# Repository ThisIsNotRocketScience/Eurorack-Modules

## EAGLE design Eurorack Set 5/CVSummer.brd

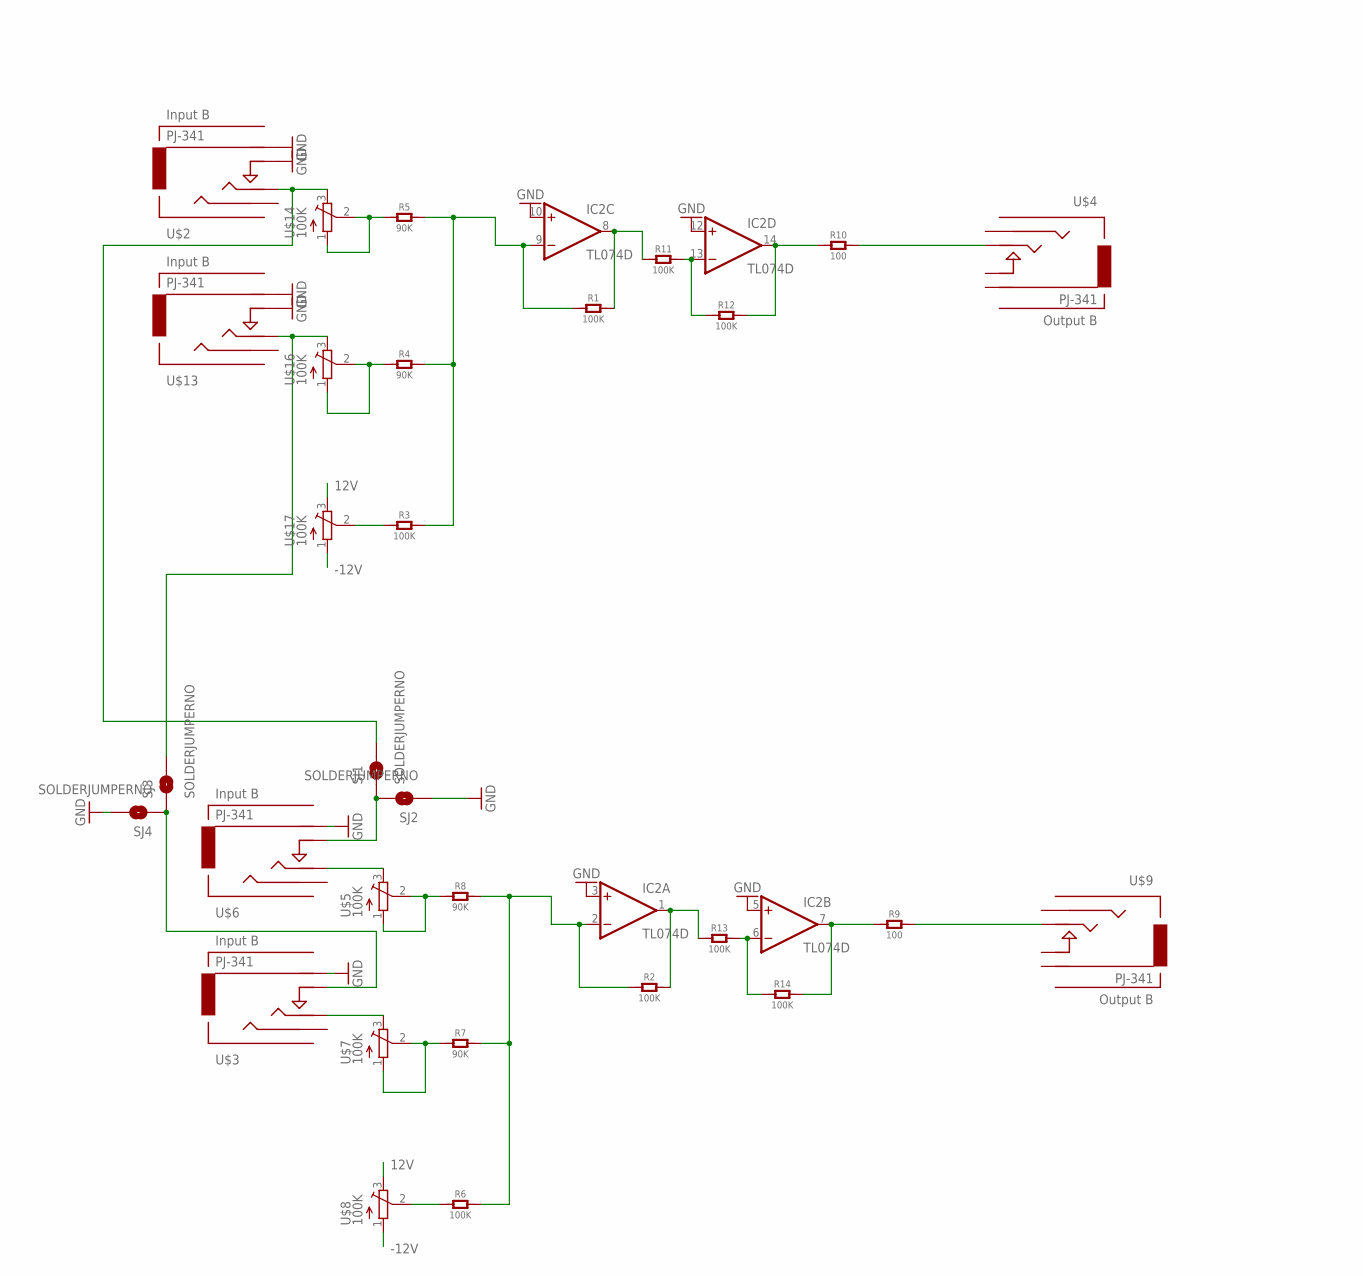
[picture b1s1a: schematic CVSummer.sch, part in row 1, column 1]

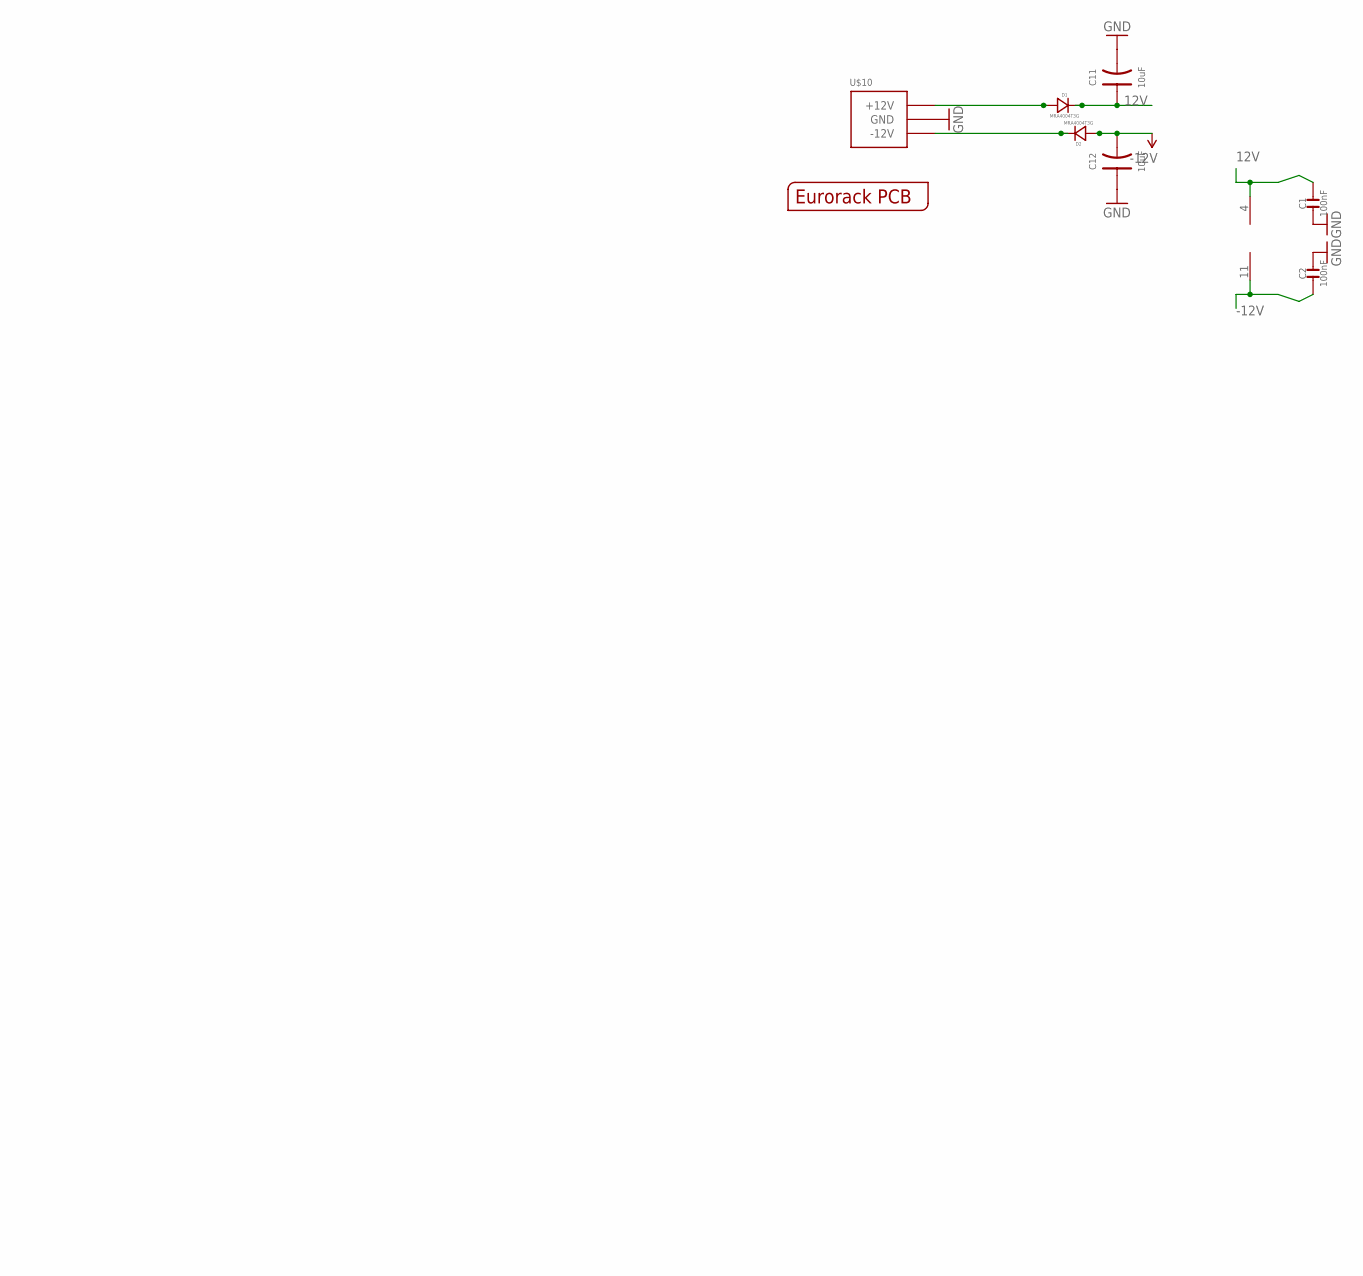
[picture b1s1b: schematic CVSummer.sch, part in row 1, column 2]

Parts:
C1, C2: 100nF; C0603
C11, C12: 10uF; AVX-A
D1, D2: MRA4004T3G; DO-214AC; MPN US1G-E3/5AT
IC2: TL074D; SO14
R1, R2, R3, R6, R11, R12, R13, R14: 100K; C0805
R4, R5, R7, R8: 90K; C0805
R9, R10: 100; C0805
SJ1, SJ2, SJ3, SJ4: SOLDERJUMPERNO; SJ_2S-NO
U$1: EURORACK_PCB4HP; EURORACK4HPPCB
U$2, U$3, U$6, U$13: PJ-341; 3.5MM-JACK-SWITCH-13MM-INPUT
U$4, U$9: PJ-341; 3.5MM-JACK-SWITCH-13MM-OUTPUT
U$5, U$7, U$8, U$14, U$16, U$17: 100K; TC33X
U$10: POWER_SIMPLE10; POWER_10

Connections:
12V: C1.2, C11.+ (1), D1.2 (-), IC2.4 (V+), U$8.3 (E), U$17.3 (E)
-12V: C2.1, C12.- (2), D2.1 (+), IC2.11 (V-), U$8.1 (A), U$17.1 (A)
GND: C1.1, C2.2, C11.- (2), C12.+ (1), IC2.3 (+IN), IC2.5 (+IN), IC2.10 (+IN), IC2.12 (+IN), SJ2.1, SJ4.2, U$2.RING@3 (RING), U$2.SWITCH@3 (SWITCH), U$3.RING@3 (RING), U$6.RING@3 (RING), U$10.3 (GND), U$10.4 (GND), U$10.5 (GND), U$10.6 (GND), U$10.7 (GND), U$10.8 (GND), U$13.RING@3 (RING), U$13.SWITCH@3 (SWITCH)
unnamed: SJ1.1, SJ2.2, U$6.SWITCH@3 (SWITCH)
unnamed: IC2.14 (OUT), R10.1, R12.2
unnamed: R5.1, U$14.1 (A), U$14.2 (S)
unnamed: U$5.3 (E), U$6.TIP@3 (TIP)
unnamed: IC2.7 (OUT), R9.1, R14.2
unnamed: R3.1, U$17.2 (S)
unnamed: IC2.8 (OUT), R1.2, R11.1
unnamed: IC2.13 (-IN), R11.2, R12.1
unnamed: R6.1, U$8.2 (S)
unnamed: R4.1, U$16.1 (A), U$16.2 (S)
unnamed: U$3.TIP@3 (TIP), U$7.3 (E)
unnamed: SJ3.2, U$13.TIP@3 (TIP), U$16.3 (E)
unnamed: IC2.2 (-IN), R2.1, R6.2, R7.2, R8.2
unnamed: IC2.9 (-IN), R1.1, R3.2, R4.2, R5.2
unnamed: R9.2, U$9.TIP@3 (TIP)
unnamed: R8.1, U$5.1 (A), U$5.2 (S)
unnamed: R7.1, U$7.1 (A), U$7.2 (S)
unnamed: IC2.1 (OUT), R2.2, R13.1
unnamed: IC2.6 (-IN), R13.2, R14.1
unnamed: SJ1.2, U$2.TIP@3 (TIP), U$14.3 (E)
unnamed: SJ3.1, SJ4.1, U$3.SWITCH@3 (SWITCH)
unnamed: R10.2, U$4.TIP@3 (TIP)
unnamed: D1.1 (+), U$10.9 (+12V), U$10.10 (+12V)
unnamed: D2.2 (-), U$10.1 (-12V), U$10.2 (-12V)

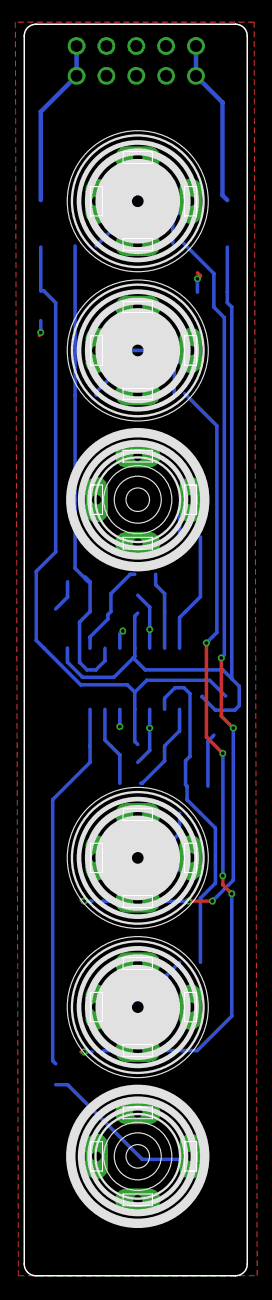
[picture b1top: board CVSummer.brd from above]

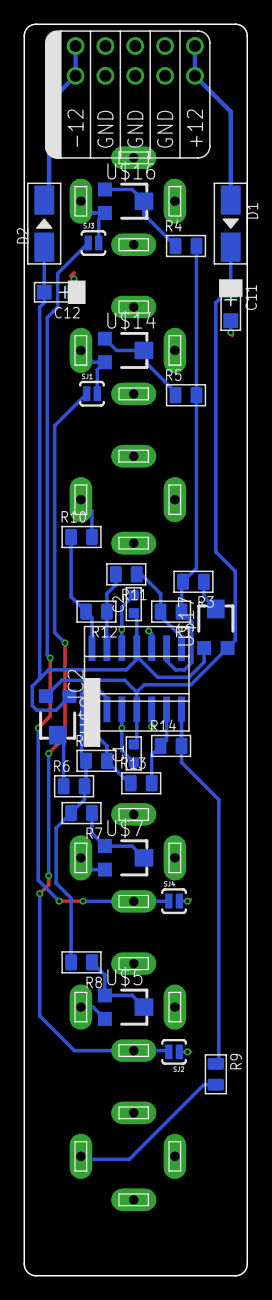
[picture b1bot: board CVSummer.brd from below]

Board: 2 copper layers, 19.0 x 106.5 mm, 39 parts (32 on the bottom side), 27 nets.

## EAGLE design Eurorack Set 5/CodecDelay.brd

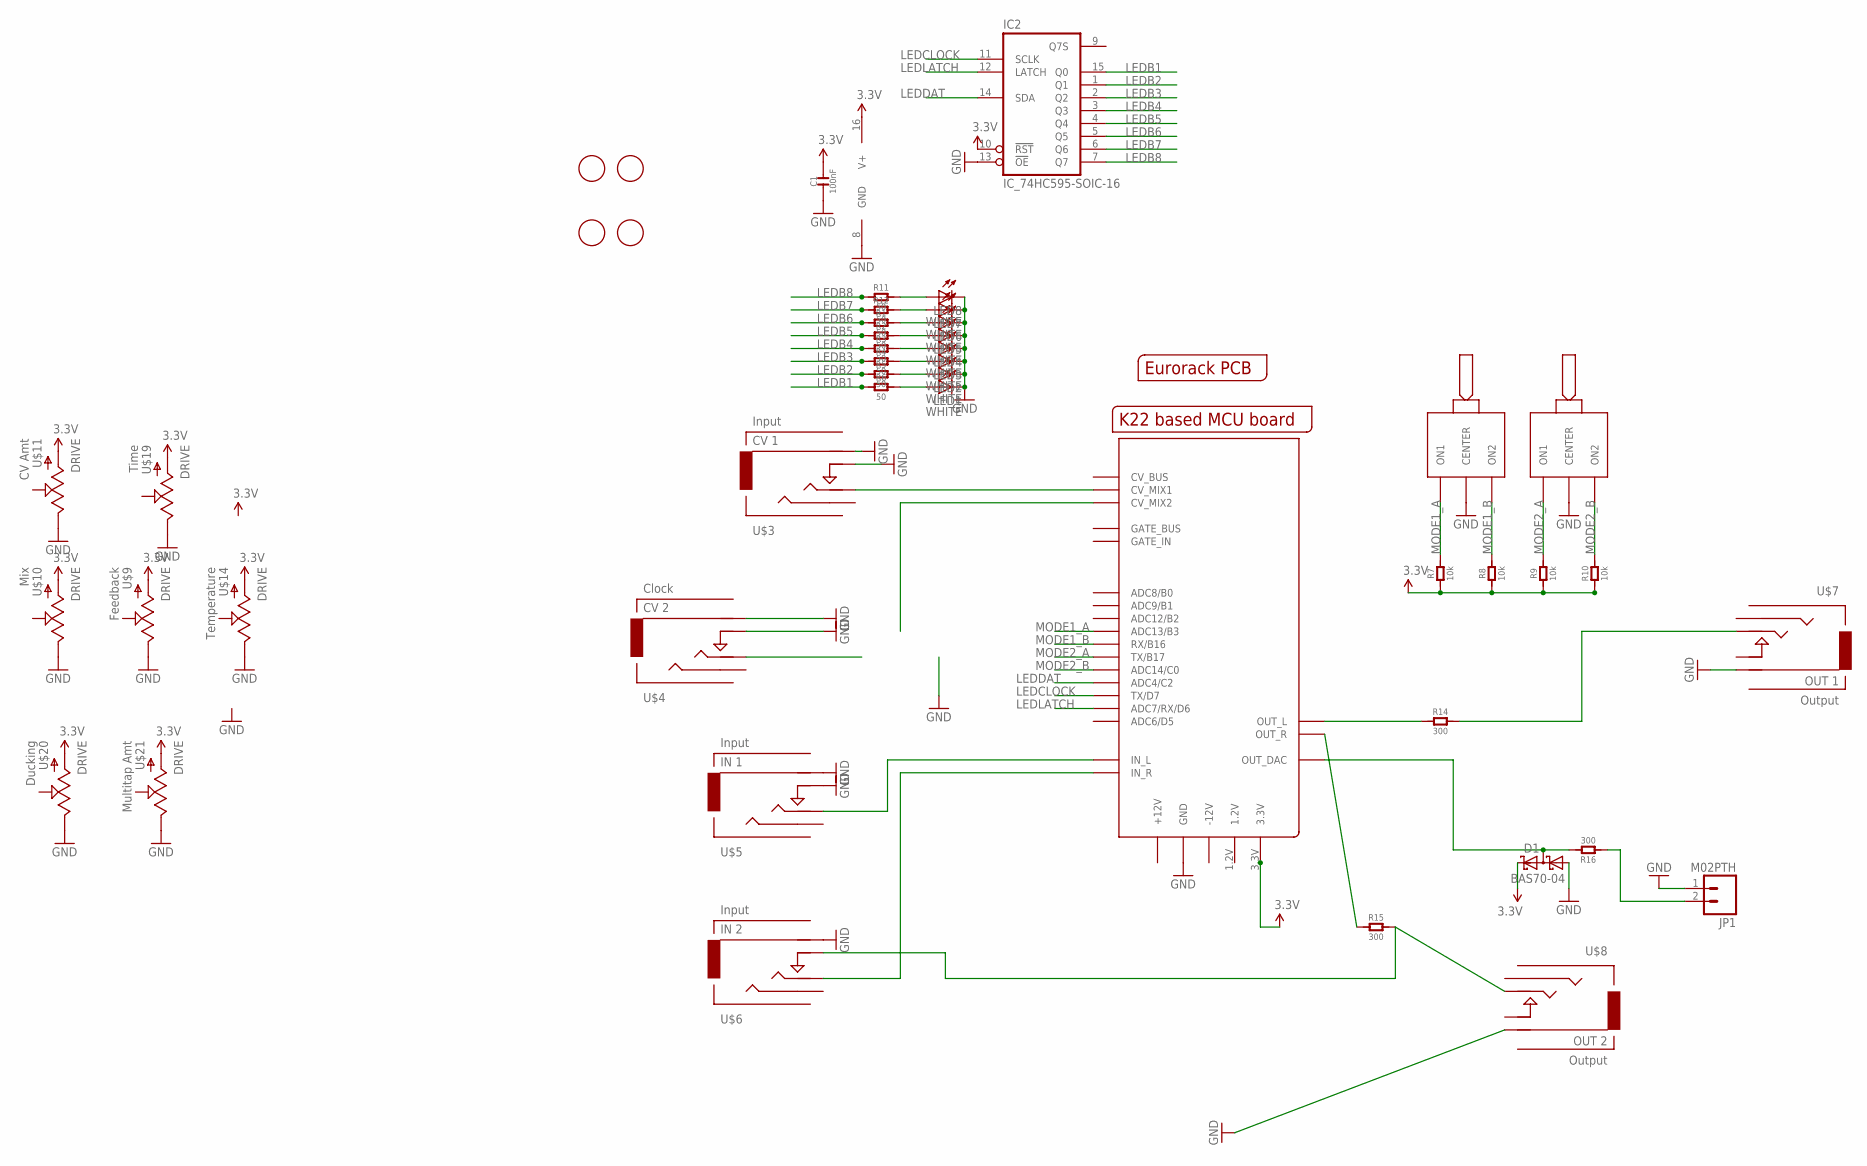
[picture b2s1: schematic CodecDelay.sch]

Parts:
C1: 100nF; C0603
D1: BAS70-04; SOT23
IC2: IC_74HC595-SOIC-16; SOIC-16
JP1: M02PTH; 1X02
LED1, LED2, LED3, LED4, LED5, LED6, LED7, LED8: WHITE; LED3MM
R1, R2, R3, R4, R5, R6, R11, R12: 50; R0603
R7, R8, R9, R10: 10k; R0603
R14, R15: 300; C0805
R16: 300; R0603
U$1: MCUBOARD; MCUBASEBOARD
U$2: EURORACK_PCB8HP; EURORACK8HPPCB
U$3: CV 1; 3.5MM-JACK-SWITCH-13MM-INPUT
U$4: CV 2; 3.5MM-JACK-SWITCH-13MM-INPUT
U$5: IN 1; 3.5MM-JACK-SWITCH-13MM-INPUT
U$6: IN 2; 3.5MM-JACK-SWITCH-13MM-INPUT
U$7: OUT 1; 3.5MM-JACK-SWITCH-13MM-OUTPUT
U$8: OUT 2; 3.5MM-JACK-SWITCH-13MM-OUTPUT
U$9, U$10, U$11, U$14, U$19, U$20, U$21: DRIVE; OG-POTS_ALPS_POT_VERTICAL
U$12, U$13: ONOFFON; MULTICOMP1MS-ONOFFON
U$15, U$16, U$17, U$18: FIDUCIAL; FIDUCIAL_1MM

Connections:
3.3V: C1.2, D1.2 (C2), IC2.10 (!RST), IC2.16 (V+), R7.1, R8.1, R9.1, R10.1, U$1.3.3V, U$9.P$3 (A), U$10.P$3 (A), U$11.P$3 (A), U$14.P$3 (A), U$19.P$3 (A), U$20.P$3 (A), U$21.P$3 (A)
GND: C1.1, D1.1 (A1), IC2.8 (GND), IC2.13 (!OE), JP1.1, LED1.K (C), LED2.K (C), LED3.K (C), LED4.K (C), LED5.K (C), LED6.K (C), LED7.K (C), LED8.K (C), U$1.GND@1 (GND), U$1.GND@2 (GND), U$1.GND@4 (GND), U$1.GND@5 (GND), U$1.GND@6 (GND), U$1.GND@7 (GND), U$1.GND@8 (GND), U$1.GND@9 (GND), U$1.GND_BUS (GND), U$3.RING@3 (RING), U$3.SWITCH@3 (SWITCH), U$4.RING@3 (RING), U$4.SWITCH@3 (SWITCH), U$5.RING@3 (RING), U$5.SWITCH@3 (SWITCH), U$6.RING@3 (RING), U$7.RING@3 (RING), U$8.RING@3 (RING), U$9.P$1 (E), U$10.P$1 (E), U$11.P$1 (E), U$12.2 (CENTER), U$13.2 (CENTER), U$14.P$1 (E), U$19.P$1 (E), U$20.P$1 (E), U$21.P$1 (E)
LEDB1: IC2.15 (Q0), R6.1
LEDB2: IC2.1 (Q1), R5.1
LEDB3: IC2.2 (Q2), R4.1
LEDB4: IC2.3 (Q3), R3.1
LEDB5: IC2.4 (Q4), R2.1
LEDB6: IC2.5 (Q5), R1.1
LEDB7: IC2.6 (Q6), R12.1
LEDB8: IC2.7 (Q7), R11.1
LEDCLOCK: IC2.11 (SCLK), U$1.TX/D7
LEDDAT: IC2.14 (SDA), U$1.ADC4 (ADC4/C2)
LEDLATCH: IC2.12 (LATCH), U$1.ADC7 (ADC7/RX/D6)
MODE1_A: R7.2, U$1.ADC13 (ADC13/B3), U$12.1 (ON1)
MODE1_B: R8.2, U$1.RX/B16, U$12.3 (ON2)
MODE2_A: R9.2, U$1.TX/B17, U$13.1 (ON1)
MODE2_B: R10.2, U$1.ADC14 (ADC14/C0), U$13.3 (ON2)
unnamed: U$1.IN_L, U$5.TIP@3 (TIP)
unnamed: U$1.IN_R, U$6.TIP@3 (TIP)
unnamed: U$1.CV_MIX1, U$3.TIP@3 (TIP)
unnamed: R14.2, U$7.TIP@3 (TIP)
unnamed: R15.2, U$6.SWITCH@3 (SWITCH), U$8.TIP@3 (TIP)
unnamed: LED1.A, R6.2
unnamed: LED2.A, R5.2
unnamed: R14.1, U$1.OUT_L
unnamed: R15.1, U$1.OUT_R
unnamed: D1.3 (C1A2), R16.2, U$1.OUT_DAC
unnamed: LED3.A, R4.2
unnamed: LED4.A, R3.2
unnamed: LED5.A, R2.2
unnamed: LED6.A, R1.2
unnamed: LED7.A, R12.2
unnamed: LED8.A, R11.2
unnamed: JP1.2, R16.1

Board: 2 copper layers, 48 parts (18 on the bottom side), 34 nets, no tracks yet.

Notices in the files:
parts and their libraries:
SparkFun-Passives: Licensing: CC v3.0 Share-Alike You are welcome to use this library for commercial purposes.
